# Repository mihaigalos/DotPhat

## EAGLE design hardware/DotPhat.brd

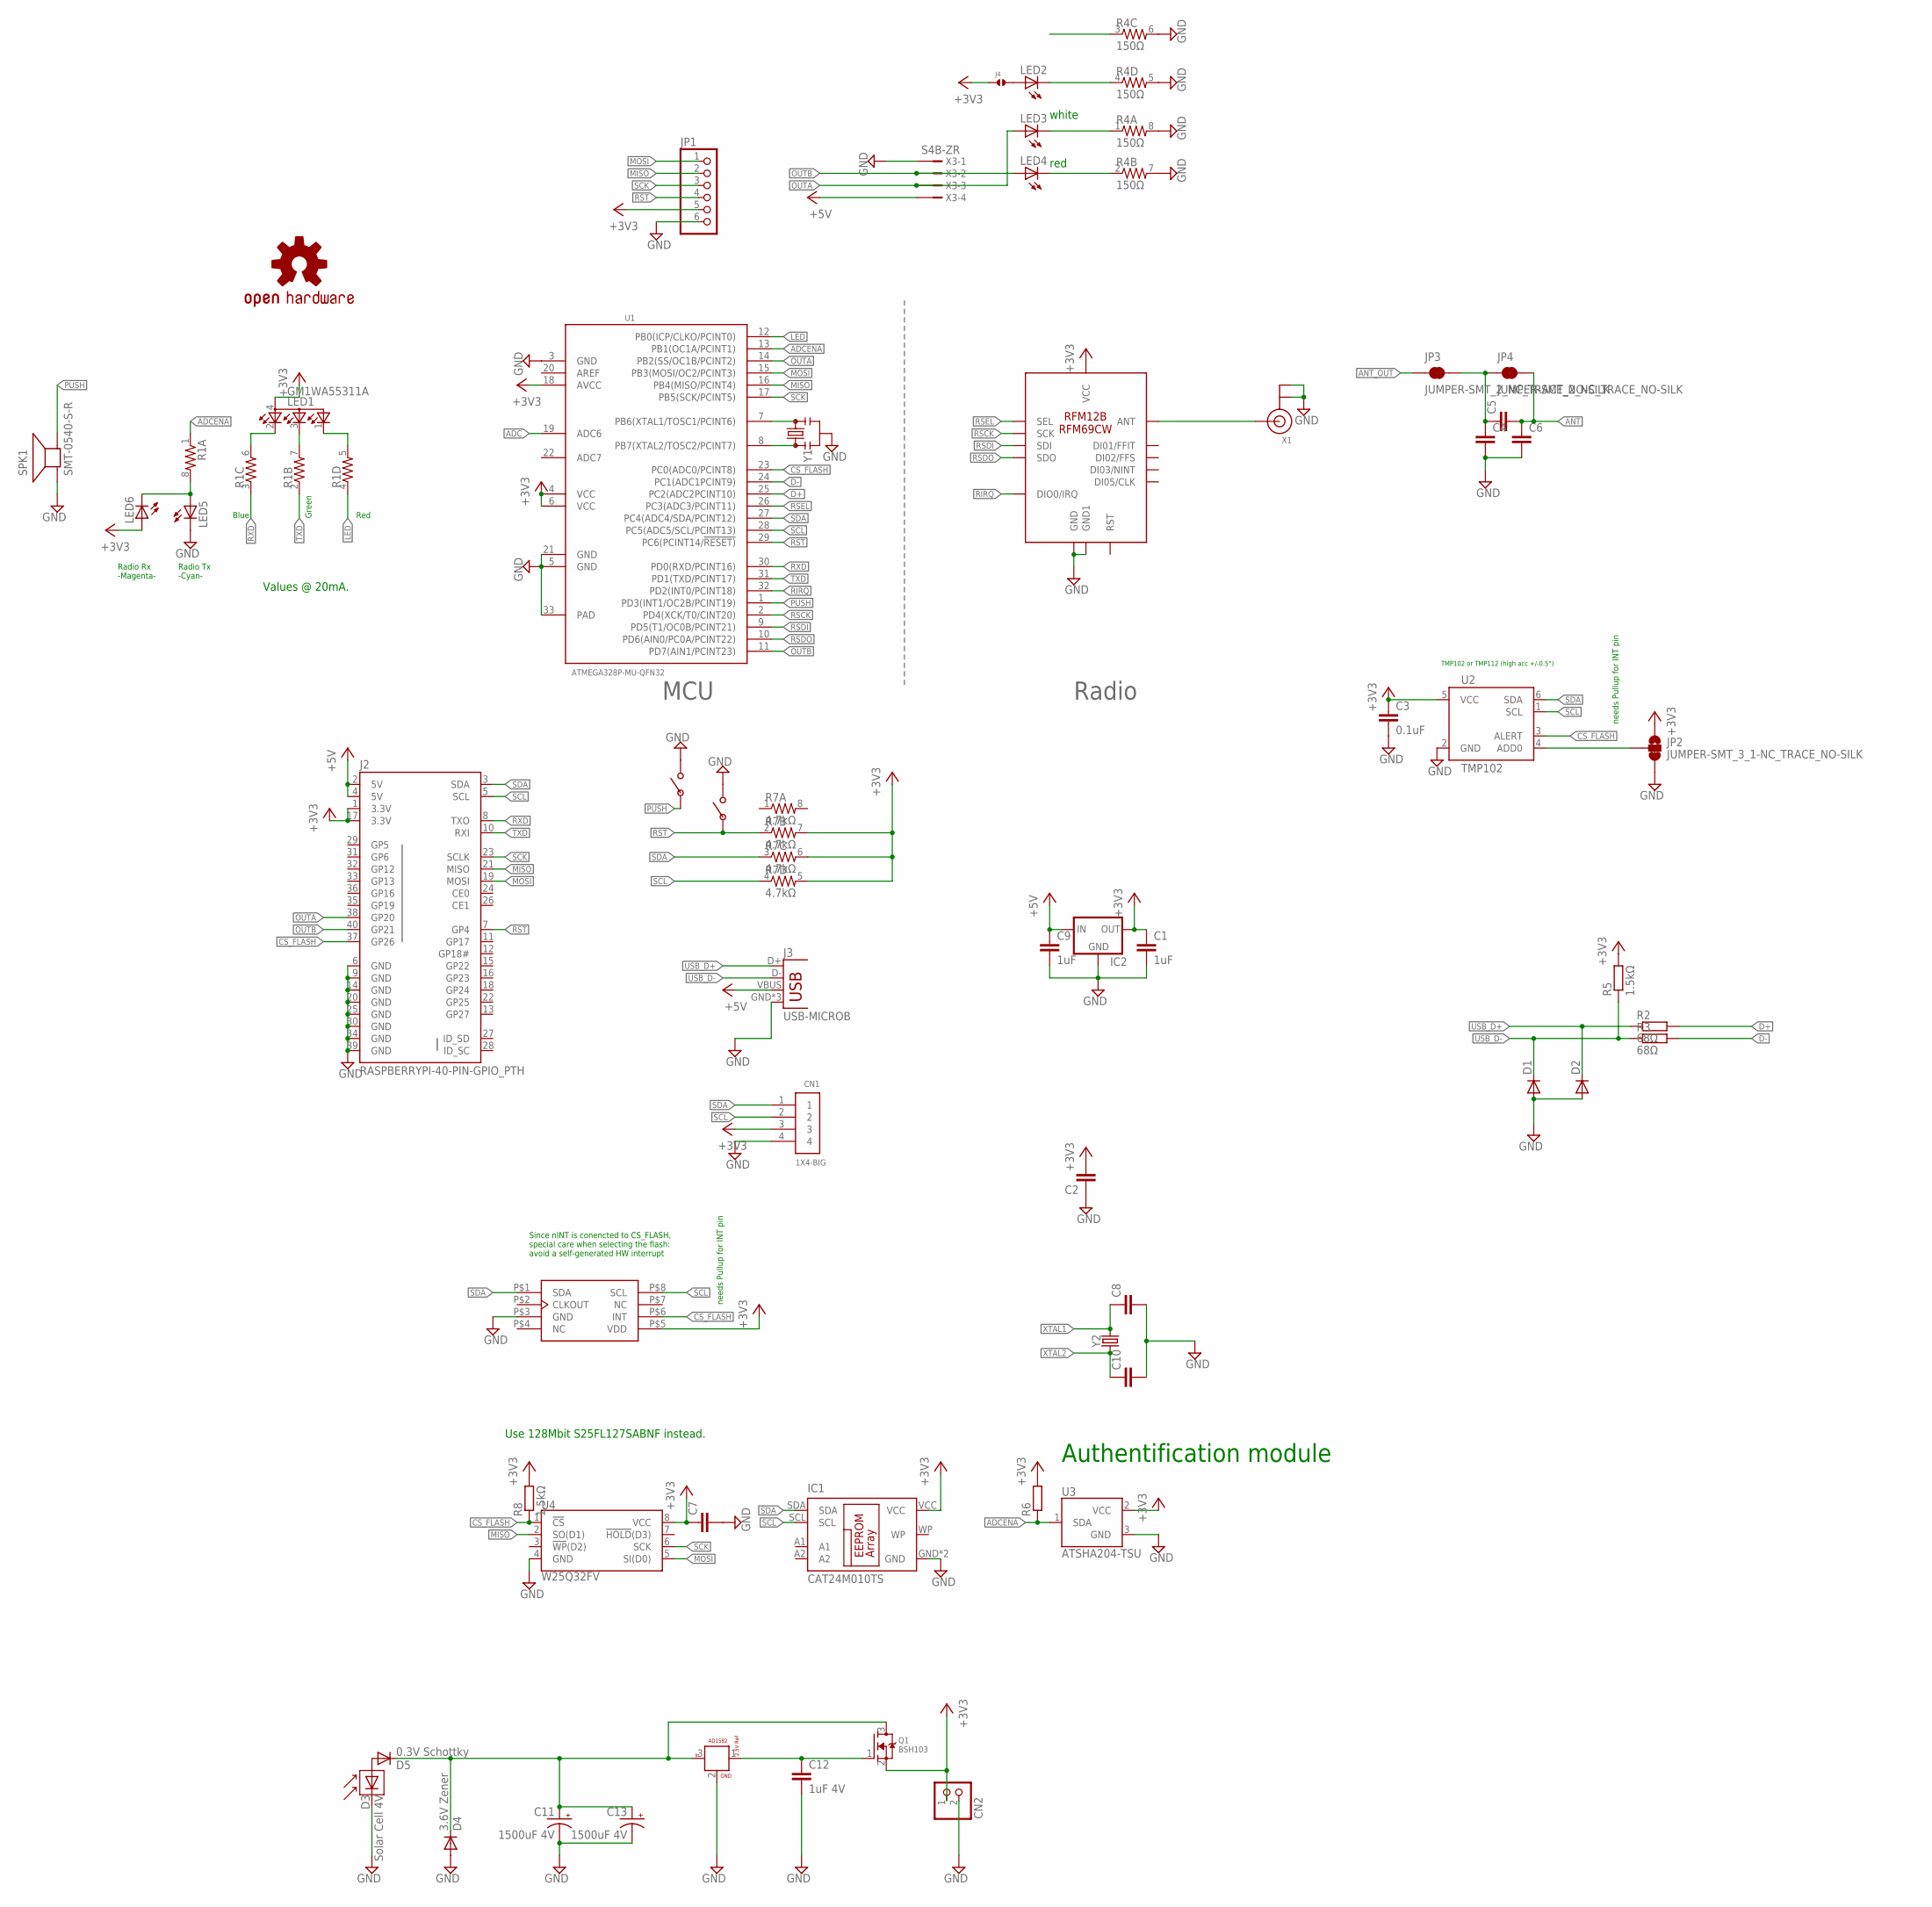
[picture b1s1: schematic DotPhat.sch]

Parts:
C1, C9: 1uF; C0603
C2: C-EUC3216; C3216
C3: 0.1uF; C0603
C4, C5, C6, C7: C-EUC0603; C0603
C8, C10: C-EUC0402; C0402
C11, C13: 1500uF 4V; CT7343
C12: 1uF 4V; C0603
CN1: 1X4-BIG; 1X04-BIG
CN2: JST_2PIN-SMT-RA; JST-PH-2-SMT-RA
D1, D2: DIODE-SOD523; SOD523
D3: Solar Cell 4V; SOLARBIT-12X1
D4: 3.6V Zener; SOD523
D5: 0.3V Schottky; SOD523
IC1: CAT24M010TS; TSSOP8
IC2: MCP1700TT; SOT-23
J2: RASPBERRYPI-40-PIN-GPIO_PTH; 2X20_SHROUDED
J3: USB-MICROB
J4: SOLDERJUMPER.2.MED; 2.MED
JP1: PINHD-1X6; 1X06
JP2: JUMPER-SMT_3_1-NC_TRACE_NO-SILK; SMT-JUMPER_3_1-NC_TRACE_NO-SILK
JP3, JP4: JUMPER-SMT_2_NC_TRACE_NO-SILK; SMT-JUMPER_2_NC_TRACE_NO-SILK
LED1: GM1WA55311A
LED2, LED3, LED4, LED5, LED6: LED0603; LED-0603
LOGO1: OSHW-LOGOS; OSHW-LOGO-S
Q1: BSH103; SOT23
R1: RESISTOR-ARRAY0603-ARV; 0603-ARV
R2, R3: 68Ω; R0603
R4: 150Ω; 0603-ARV
R5, R8: 1.5kΩ; R0603
R6: R-EU_R0603; R0603
R7: 4.7kΩ; 0603-ARV
SPK1: SMT-0540-S-R
U1: ATMEGA328P-MU-QFN32; QFN32G-0.5-5X5MM
U2: TMP102; SOT563
U3: ATSHA204-TSU; SOT23-3
U4: W25Q32FV; WSON8-6X5MM
U$1: RFM12B/69CW
U$2, U$3: PUSHBUTTON_4X2.5
U$4: AD1582; SOT23
X1: ANTENNA_U.FL; U.FL
X2: MC-RTC-RV-4162-C7-I2C; MC-RTC-C7
X3: S4B-ZR
Y1: RESONATORSMD-3.2X1.3; RESONATOR-SMD-3.2X1.3
Y2: CRYSTALSMD-3.2X1.5; CRYSTAL-SMD-3.2X1.5MM

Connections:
+3V3: C1.1, C2.2, C3.1, C7.1, CN1.3, CN2.1 (2), IC1.VCC, IC2.2 (OUT), J2.1 (3.3V), J2.17 (3.3V), J4.1, JP1.5, JP2.1, LED1.4 (A), LED6.A, Q1.2 (S), R5.2, R6.2, R7.5 (2), R7.6 (2), R7.7 (2), R8.2, U1.4 (VCC), U1.6 (VCC), U1.18 (AVCC), U2.5 (VCC), U3.2 (VCC), U4.8 (VCC), U$1.VDD (VCC), X2.P$5 (VDD)
+5V: C9.1, IC2.3 (IN), J2.2 (5V), J2.4 (5V), J3.VBUS, X3.4
ADC: U1.19 (ADC6)
ADCENA: R1.1, R6.1, U1.13 (PB1(OC1A/PCINT1)), U3.1 (SDA)
ANT: C5.2, C6.1, JP4.2
ANT_OUT: JP3.1, U$1.ANT, X1.3 (SIGNAL)
CAPS_VCC: C11.+, C13.+, D4.C, D5.C, Q1.3 (D), U$4.3
CS_FLASH: J2.37 (GP26), R8.1, U1.23 (PC0(ADC0/PCINT8)), U2.3 (ALERT), U4.1 (!CS!), X2.P$6 (INT)
D+: R2.2, U1.25 (PC2(ADC2PCINT10))
D-: R3.2, U1.24 (PC1(ADC1PCINT9))
GND: C1.2, C2.1, C3.2, C4.2, C6.2, C7.2, C8.2, C9.2, C10.2, C11.-, C12.2, C13.-, CN1.4, CN2.2 (1), D1.A, D2.A, D3.- (C), D4.A, IC1.GND, IC1.NC (GND), IC2.1 (GND), J2.6 (GND), J2.9 (GND), J2.14 (GND), J2.20 (GND), J2.25 (GND), J2.30 (GND), J2.34 (GND), J2.39 (GND), J3.GND, J3.MT1 (GND), J3.MT2 (GND), JP1.6, JP2.3, LED5.C, R4.5 (2), R4.6 (2), R4.7 (2), R4.8 (2), SPK1.- (+), U1.3 (GND), U1.5 (GND), U1.21 (GND), U1.33 (PAD), U2.2 (GND), U3.3 (GND), U4.4 (GND), U$1.GND, U$1.GND1, U$2.P$2, U$3.P$2, U$4.2, X1.1 (GND), X1.2 (GND), X2.P$3 (GND), X3.1, Y1.2
LED: R1.4 (1), U1.12 (PB0(ICP/CLKO/PCINT0))
MISO: J2.21 (MISO), JP1.2, U1.16 (PB4(MISO/PCINT4)), U4.2 (SO(D1))
MOSFET: C12.1, Q1.1 (G), U$4.1
MOSI: J2.19 (MOSI), JP1.1, U1.15 (PB3(MOSI/OC2/PCINT3)), U4.5 (SI(D0))
unnamed: LED1.3 (CBLUE), R1.7 (2)
unnamed: LED3.C, R4.1
unnamed: C4.1, C5.1, JP3.2, JP4.1
unnamed: LED1.2 (CRED), R1.6 (2)
unnamed: D3.+ (A), D5.A
unnamed: U1.7 (PB6(XTAL1/TOSC1/PCINT6)), Y1.3
unnamed: LED2.C, R4.4 (1)
unnamed: U1.8 (PB7(XTAL2/TOSC2/PCINT7)), Y1.1
unnamed: LED4.C, R4.2 (1)
unnamed: JP2.2, U2.4 (ADD0)
unnamed: J4.2, LED2.A
unnamed: LED5.A, LED6.C, R1.8 (2)
unnamed: LED1.1 (CGREEN), R1.5 (2)
OUTA: J2.38 (GP20), LED3.A, U1.14 (PB2(SS/OC1B/PCINT2)), X3.3
OUTB: J2.40 (GP21), LED4.A, U1.11 (PD7(AIN1/PCINT23)), X3.2
PUSH: SPK1.+ (-), U1.1 (PD3(INT1/OC2B/PCINT19)), U$3.P$1
RIRQ: U1.32 (PD2(INT0/PCINT18)), U$1.IRQ (DIO0/IRQ)
RSCK: U1.2 (PD4(XCK/T0/CINT20)), U$1.SCK
RSDI: U1.9 (PD5(T1/OC0B/PCINT21)), U$1.SDI
RSDO: U1.10 (PD6(AIN0/PC0A/PCINT22)), U$1.SDO
RSEL: U1.26 (PC3(ADC3/PCINT11)), U$1.SEL
RST: J2.7 (GP4), JP1.4, R7.2 (1), U1.29 (PC6(PCINT14/!RESET)), U$2.P$1
RXD: J2.8 (TXO), R1.3 (1), U1.30 (PD0(RXD/PCINT16))
SCK: J2.23 (SCLK), JP1.3, U1.17 (PB5(SCK/PCINT5)), U4.6 (SCK)
SCL: CN1.2, IC1.SCL, J2.5 (SCL), R7.4 (1), U1.28 (PC5(ADC5/SCL/PCINT13)), U2.1 (SCL), X2.P$8 (SCL)
SDA: CN1.1, IC1.SDA, J2.3 (SDA), R7.3 (1), U1.27 (PC4(ADC4/SDA/PCINT12)), U2.6 (SDA), X2.P$1 (SDA)
TXD: J2.10 (RXI), R1.2 (1), U1.31 (PD1(TXD/PCINT17))
USB_D+: D2.C, J3.D+, R2.1
USB_D-: D1.C, J3.D-, R3.1, R5.1
XTAL1: C8.1, Y2.P$2 (2)
XTAL2: C10.1, Y2.P$1 (1)

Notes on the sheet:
MCU
Radio
Values @ 20mA.
Blue
Green
Red
TMP102 or TMP112 (high acc +/-0.5°)
Authentification module
white
red
Use 128Mbit S25FL127SABNF instead.
Since nINT is conencted to CS_FLASH, special care when selecting the flash: avoid a self-generated HW interrupt
needs Pullup for INT pin
Radio Rx -Magenta-
Radio Tx -Cyan-

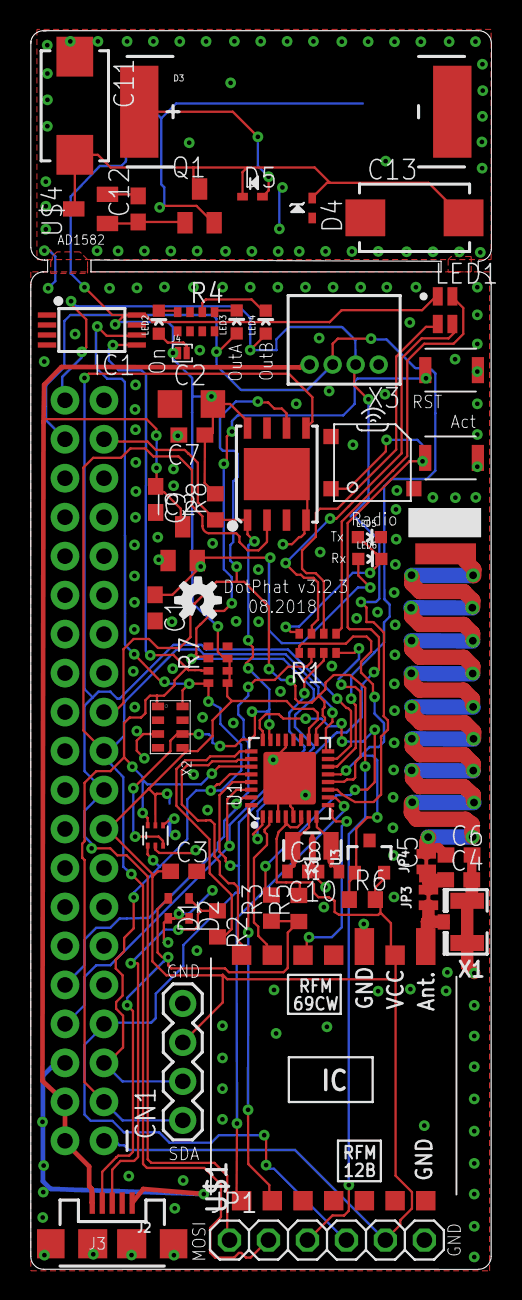
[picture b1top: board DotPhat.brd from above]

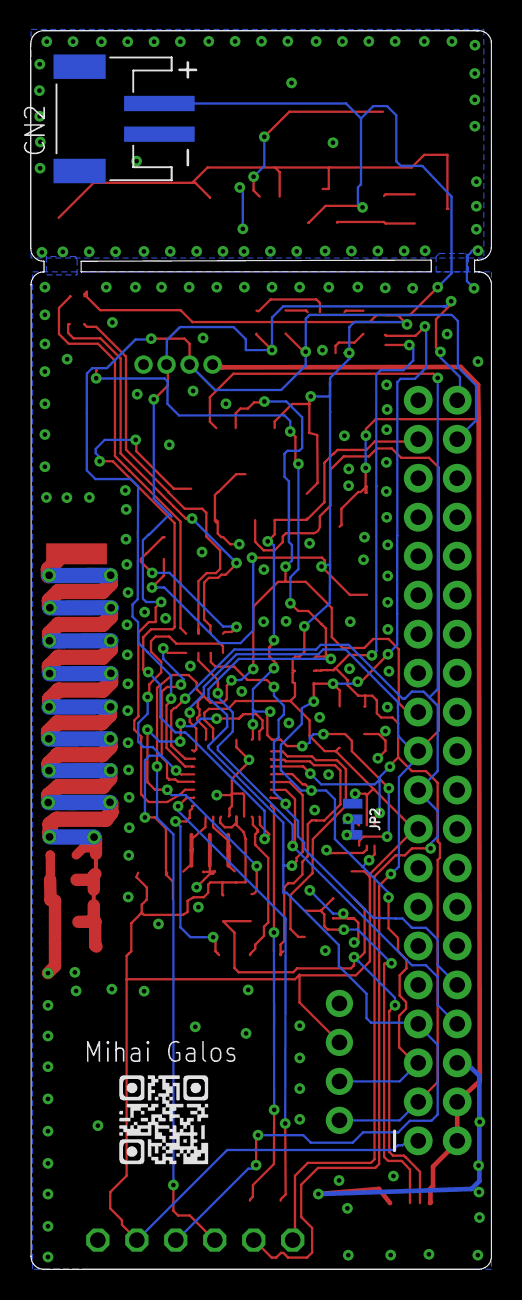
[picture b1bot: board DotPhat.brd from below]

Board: 2 copper layers, 30.0 x 80.7 mm, 59 parts (2 on the bottom side), 45 nets.

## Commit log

2017-10-06 Initial version
2017-10-06 Add 2 out JST connectors, solid GND vias
2017-10-07 Replace JST2 with JST4, add leds for channels
2017-10-07 amend
2017-10-15 Swap 5V and GND for the JST to match cable color
2017-10-21 Add microusb
2017-10-21 Add I2C
2017-10-21 Improving GND
2017-10-21 Add radio led
2017-10-21 Add HexId, ISM Bands
2017-10-21 Make JST compatible with generic relays
2017-10-21 Update with RPi lib with no tPlace
2017-10-21 Add mandatory 5V-3.3V capless regulator for USB power
2017-10-22 Add filter cap at 3.3V regulator out pin
2017-10-22 Replace RGB resistors for array
2017-10-22 Add TMP112 temperature sensor
2017-11-03 Add USB programming connections
2017-11-03 Update version info
2017-11-03 Add rounded corners
2017-11-04 Add I2C E2PROM
2017-11-05 Move vias away from R array
2017-11-05 Update labels
2017-11-05 Add CryptoAuthentication module
2017-11-05 Reposition new components
2017-11-07 Make USB_D+ and USB_D- part of the same port. Required for Micronucleus.
2017-11-07 Updating version
2017-11-08 Add pullup on SDA for crypto & bypass cap
2017-12-26 Add PCB Antenna
2017-12-26 Add Pi-network for antenna matching
2017-12-26 Rearrange USB and OUT connectors
2017-12-26 Add support for high-precision chrystal
2017-12-26 Correct via
2017-12-26 :spaceinvaders: Add .gitattributes and .gitignore
2017-12-28 Flip uFL to top side
2017-12-28 Switch to SMD buzzer
2017-12-28 Reposition antenna PI-filter
2017-12-28 Improve GND
2018-01-16 checkpoint
2018-02-03 Correct short-circuit
2018-02-04 Update USB pullup to downside, 3.3V instead of 5V
2018-02-25 Update actor leds' color in schematic
2018-03-21 Initial DotPhat case
2018-03-21 Add microusb and relay cuts
2018-03-21 Semifinal design
2018-03-23 Update case
2018-03-23 Case v2
2018-03-23 Add revised case
2018-03-26 Add 128Mbit SPI Flash
2018-03-30 Add RTC chip, plug irqs from sensors, flash
2018-03-30 Switch to low quiescent LDO
2018-03-30 Update version
2018-03-30 Drive OutX from Pi, additionally
2018-05-03 Add jumper for power led
2018-05-05 Add logic for sending and receiving RF. Not yet tested.
2018-05-09 Add radio activity led
2018-05-09 Update initial system state
2018-05-09 Add TRx leds for radio communication, improve GND
2018-05-09 Add e2prom metadata support
2018-05-10 Add eeprom dump
2018-05-12 Add push reset and action
2018-05-13 Add firmware code for eeprom metadata
2018-05-13 Add app spin
2018-05-16 Correct Rx led polarity
2018-06-06 Beta: Add solar supply with caps
2018-06-07 Beta: Simplify solar power supply
2018-06-13 Receive working during usb spin
2018-06-14 Fix send command repeat and frequency parsing
2018-07-21 PoC: Ledmenu
2018-07-21 Improve PoC for ledmenu
2018-07-22 Working implementation of 1-button menu
2018-07-24 Add I2C read handler
2018-07-27 Add I2C Callback, vcc to blinks
2018-07-30 Add I2C write byte
2018-08-01 Correct i2c read
2018-09-27 Use supercap from library
2018-10-03 Extend static eeprom data
2018-10-03 Optimize RF to leds
2018-10-05 Add support for TRX led
2018-10-05 Add temperature to rgb
2018-10-05 Add temperature fractional part
2018-10-31 endTransmission(false), clang-format
2018-11-30 Add prescaler for smooth running under 3V
2020-04-10 Replace comments with types
2020-04-10 Refactor eeprom config to separate file
2020-04-10 Move update function to central eeprom_metadata.h
2020-04-10 Move constants to config.h
2020-04-10 Refactor logic to separate files
2020-04-10 Refactor temperature to leds to separate file
2020-04-10 Apply clang-format
2020-04-10 Move radio send logic to radio.h
2020-04-10 Improve naming

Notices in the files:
parts and their libraries:
SparkFun: Licensing: CC v3.0 Share-Alike You are welcome to use this library for commercial purposes.
SparkFun-Clocks: Licensing: Creative Commons ShareAlike 4.0 International - https://creativecommons.org/licenses/by-sa/4.0
